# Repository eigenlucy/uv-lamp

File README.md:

# uv-lamp
Open source flashlight kit

Made with atopile/KiCad

Ordering UVA-UVC flashlights on Amazon is notoriously a crapshoot. This project is designed to enable easy use of quality diodes instead :)

You can order a kit or an assembled unit from my tindie store (soonTM), or find everything you need to print and enclosure and order PCB/PCBA services below

Gerbers, BOM, and CPL files for PCBA JLCPCB PCBA services are automatically generated on each push in the build artifacts under the Actions tab

# BMS+LED Driver board:
ato.yaml :: ccdriver

entry: elec/src/ccdriver.ato

Based on the [TI BQ24040](https://www.ti.com/lit/ds/symlink/bq24045.pdf) battery charger IC (LCSC ID: C2870255) and [TI TPS61169](https://www.ti.com/lit/ds/symlink/tps61169.pdf?ts=1737056749253) LED Driver (LSCS ID: C71045)

# LED PCB
ato.yaml :: default

entry: elec/src/uv-lamp.ato

This should be manufactured as a 1.6mm thick 1W aluminum PCB rated. You should use a hot plate to assemble this for sure.

V1 designed for 1-3 3535SMD LEDs on 1.6mm aluminum core PCBs, but see instructions below to easily adapt for use with any diode you like (power/space permitting).

# Mechanical
Heatsink:
[SV-LED-214E](https://www.digikey.com/en/products/detail/ohmite/SV-LED-214E/4301037), 3D model + datasheet in mech/SV-LED-214E

Mech BOM:

x3 2-56 UNC x 5mm screws

# Atopile usage
[Atopile Docs](https://docs.atopile.io/latest/)

Atopile makes it easy to adapt this design for use with other diodes, drivers, BMS circuits, etc.

To change the LED package:

1: Fork this repo

2: Install [atopile from pypi](https://pypi.org/project/atopile/0.2.5/) with uv (recommended), pipx, or virtual fish. There is also a VCS extension for those inclined. Follow the instructions in the ato docs on setting up the kicad plugin,usually just ```$ ato configure```

3: find diodes you want/diodes using the package you want on the JLCPCB parts library, LCSC, or with [this tool](https://yaqwsx.github.io/jlcparts/#/) and install them into your project directory with 
```$ ato install --jlcpcb <LCSC_ID>```
For example, to install [WS2812B Neopixels](https://jlcpcb.com/partdetail/Worldsemi-WS2812B2020/C965555) with LCSC ID C965555:
```$ ato install --jlcpcb C965555```

4: open uv-lamp.ato in a text editor. import the module/component you've installed, eg:
```from "WS2812B_minus_2020.ato" import WS2812B_minus_2020```
check the pin names in the component ato file, and configure and interfaces you need. For other UV diodes, just ensure the pins are labeled A (anode) and K (cathode) and replace the components assigned to led1-led3:
```led1 = new M3535N1UVS8U06_minus_365NM -> led1 = new <COMPONENT>```

5: build with ```$ ato build```. to use the graph viewer on a project with multiple builds, specify the target with ```$ ato view -t ccdriver```. default build is the LED PCB.

# Downloading PCB+PCBA files for JLCPCB
Gerbers, BOM and CPL files are automatically compiled at each build in the build artifacts of the Actions run. Each build (default for LED PCB, ccdriver for the BMS+LED Driver board) get its own set of files.

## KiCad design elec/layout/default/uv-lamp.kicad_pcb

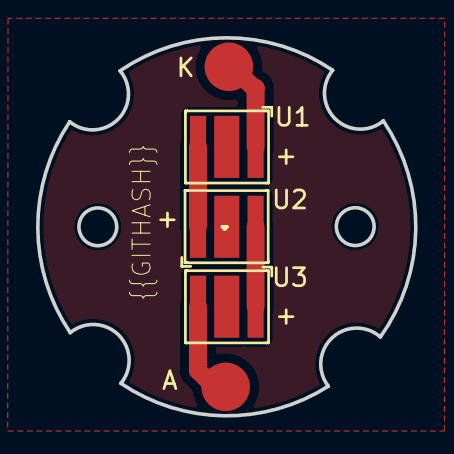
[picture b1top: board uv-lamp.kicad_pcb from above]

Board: 2 copper layers, 21.0 x 21.0 mm, 3 parts (0 on the bottom side), 2 nets.

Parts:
U1, U2, U3: LED-SMD_3P-L3.5-W3.5_M3535O1IRS13G06

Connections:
A-1: U1.1, U2.2
K: U2.1, U3.2

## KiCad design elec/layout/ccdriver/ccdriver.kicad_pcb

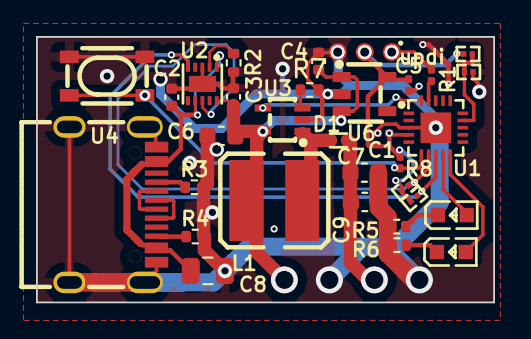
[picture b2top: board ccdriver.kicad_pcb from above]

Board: 2 copper layers, 25.4 x 14.8 mm, 31 parts (0 on the bottom side), 22 nets.

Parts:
C1: 10V 100nF X5R ±10% 0201 Multilayer Ceramic Capaci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; C0201
C2, C3, C4: 25V 1uF X5R ±10% 0402 Multilayer Ceramic Capacito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; C0402
C5: 10V 1uF X5R ±20% 0201 Multilayer Ceramic Capacito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; C0201
C6, C9: 16V 4.7uF X5R ±10% 0603 Multilayer Ceramic Capaci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; C0603
C7: 50V 1uF X5R ±10% 0603 Multilayer Ceramic Capacito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; C0603
C8: 25V 10uF X5R ±10% 0805 Multilayer Ceramic Capacit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; C0805
D1: ?; SOD-923_L0.8-W0.6-LS1.0-RD-1
L1: ?; IND-SMD_L4.5-W4.0
LED1, LED2: ?; LED0603-RD
R1: 50mW Thick Film Resistors ±5% 510Ω 0201 Chip Resi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; R0201
R2: 62.5mW Thick Film Resistors 50V ±100ppm/℃ ±1% 576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; R0402
R3, R4: 62.5mW Thick Film Resistors 50V ±100ppm/℃ ±1% 4.7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; R0402
R5: 62.5mW Thick Film Resistors 50V ±100ppm/℃ ±1% 220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; R0402
R6: 62.5mW Thick Film Resistors 50V ±1% ±200ppm/℃ 100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; R0402
R7: 62.5mW Thick Film Resistors 50V ±1% 300mΩ 0402 Ch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; R0402
R8, R9, R10, R11: 50mW Thick Film Resistors 25V ±1% ±200ppm/℃ 10kΩ 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; R0201
U1: ?; QFN-20_L3.0-W3.0-P0.40-TL-EP1.7
U2: ?; WSON-10_L2.0-W2.0-P0.40-BL-EP
U3: ?; SC-70-5_L2.1-W1.3-P0.65-LS2.1-BR
U4: ?; USB-C-SMD_KH-TYPE-C-16P
U5: ?; KEY-SMD_4P-L4.2-W3.2-P2.20-LS4.6
U6: ?; SOT-23-5_L3.0-W1.7-P0.95-LS2.8-TL
U7: ?; R0201

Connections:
bms.ic-vcc: C2.1, C8.1, U2.1, U2.7, U4.A4, U4.A9, U4.B4, U4.B9
cc1: R3.1, U4.A5
cc2: R4.1, U4.B5
charge_led.resistor-cathode: LED1.1, R5.1
chg: R10.1, U1.7, U2.8
ctrl: U1.20, U3.4
dm: U4.A7, U4.B7
dp: U4.A6, U4.B6
fb: R7.1, U3.3
full_led.resistor-cathode: LED2.1, R6.1
gnd: C1.2, C2.2, C3.2, C4.2, C5.2, C6.2, C7.2, C8.2, C9.2, R2.2, R3.2, R4.2, R5.2, R6.2, R7.2, U1.3, U1.21, U2.3, U2.11, U3.2, U4.1, U4.2, U4.3, U4.4, U4.A1, U4.A12, U4.B1, U4.B12, U5.3, U5.4, U6.2, U7.2
in: R8.1, U1.6, U5.1, U5.2
iset: R2.1, U2.2
pa0_reset_updi: R1.2, U1.19
pg: R11.1, U1.8, U2.5
sw: D1.2, L1.2, U3.1
temp: R9.2, U1.14, U7.1
uc.ic-vcc: C1.1, C5.1, R8.2, R9.1, R10.2, R11.2, U1.4, U6.5
uc.ic-vcc-1: LED1.2, U1.9
uc.ic-vcc-2: LED2.2, U1.10
vcc: C7.1, C9.1, D1.1
vcc-1: C3.1, C4.1, C6.1, L1.1, U2.10, U3.5, U6.1, U6.3

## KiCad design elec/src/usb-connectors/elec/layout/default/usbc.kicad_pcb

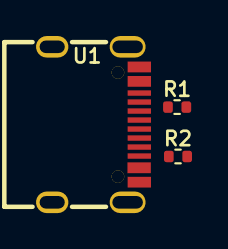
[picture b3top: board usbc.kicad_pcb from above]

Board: 2 copper layers, 3 parts (0 on the bottom side), 6 nets, no tracks yet.

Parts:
R1, R2: Chip Resistor - Surface Mount 4.7KOhms ±5% 1/16W 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; R0402
U1: USB-C-SMD_KH-TYPE-C-16P

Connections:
cc1: R1.1, U1.A5
cc2: R2.1, U1.B5
dm: U1.A7, U1.B7
dp: U1.A6, U1.B6
gnd: R1.2, R2.2, U1.1, U1.2, U1.3, U1.4, U1.A1, U1.A12, U1.B1, U1.B12
vcc: U1.A4, U1.A9, U1.B4, U1.B9

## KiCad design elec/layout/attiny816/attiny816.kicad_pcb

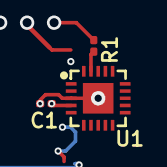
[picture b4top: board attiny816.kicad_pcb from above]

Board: 2 copper layers, 3 parts (0 on the bottom side), 3 nets.

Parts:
C1: 25V 100nF X5R ±10% 0201 Multilayer Ceramic Capaci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; C0201
R1: 50mW Thick Film Resistors ±5% 510Ω 0201 Chip Resi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; R0201
U1: ?; QFN-20_L3.0-W3.0-P0.40-TL-EP1.7

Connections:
gnd: C1.2, U1.3, U1.21
pa0_reset_updi: R1.2, U1.19
vcc: C1.1, U1.4

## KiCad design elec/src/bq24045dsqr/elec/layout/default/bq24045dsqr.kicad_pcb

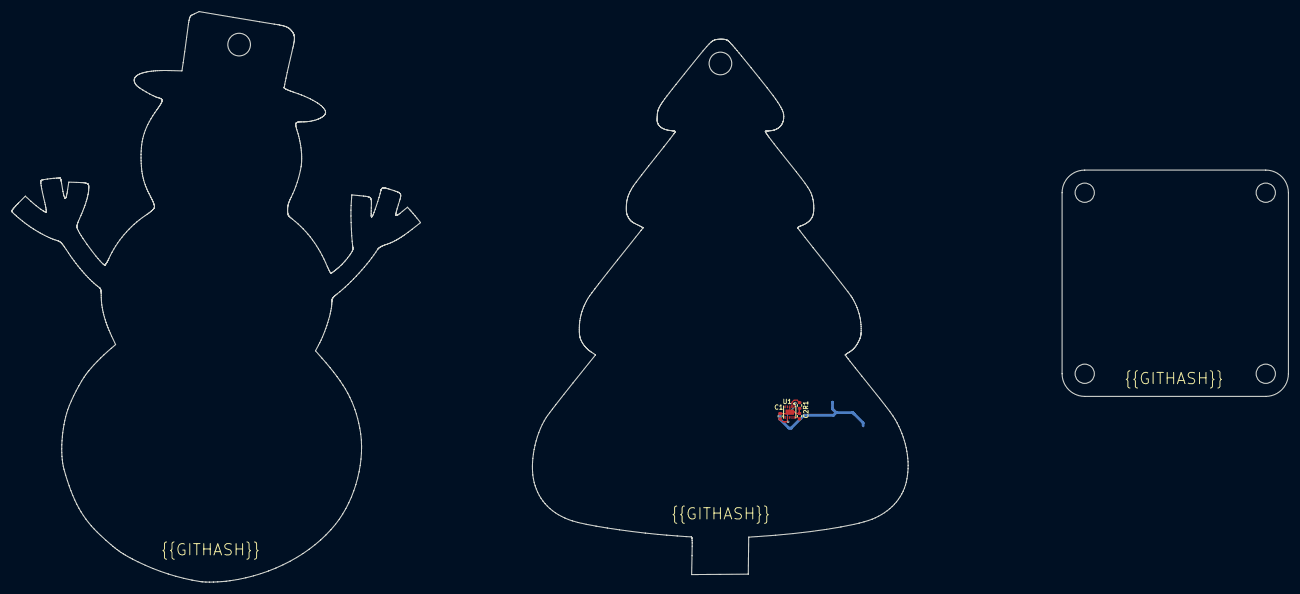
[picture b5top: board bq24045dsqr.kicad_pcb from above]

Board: 2 copper layers, 66.4 x 94.6 mm, 4 parts (0 on the bottom side), 4 nets.

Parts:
C1, C2: 25V 1uF X5R ±10% 0402 Multilayer Ceramic Capacito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; C0402
R1: 100mW Thick Film Resistors ±100ppm/℃ ±1% 604Ω 040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; R0402
U1: WSON-10_L2.0-W2.0-P0.40-BL-EP

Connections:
ic-gnd: C1.2, C2.2, R1.2, U1.3, U1.11
ic-vcc: C1.1, U1.1, U1.7
ic-vcc-1: C2.1, U1.10
iset: R1.1, U1.2

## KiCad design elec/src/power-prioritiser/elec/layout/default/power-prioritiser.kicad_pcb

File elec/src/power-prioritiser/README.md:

# Power Prioritiser ⚡️

A simple circuit to prioritise a power source over another.

This is useful for situations like a USB-charged battery operated device, where you also want it to work when connected over just USB power.

Often, cheap (and annoyingly expensive) devices neglect this circuit and shutdown when connected over USB. I find this infuriating!

This is better than merely pulling power through the charger circuit because often the inrush currents of a circuit will overwhelm the charger IC and cause it to shut down. This can even lead in the nastiest cases to a boot-loop where the device never charges from a 0% battery.

It's better than a diode because it can handle high-voltage low-priority sources than high and it doesn't have a voltage drop over the low-priority source (typically a battery).

## Limitations

Currently, the components for this circuit are bespokely selected, and aren't parametised for majorly different voltages and currents. It's designed for a USB charged, 1S LiPo powered device.

## Usage

Simple! Hook up `high_priority` and `low_priority` to your power sources, and `out` to your device.

## How it works

When the high-priority power source is connected, the P-FET's gate is pulled high, turning it off. The P-FET thereby stops the low-priority power source from powering the device, even if it's voltage is higher than the high-priority source.

### Both sources connected

### High-priority source only

### Low-priority source only

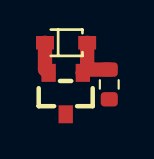
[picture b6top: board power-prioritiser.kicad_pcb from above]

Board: 2 copper layers, 3 parts (0 on the bottom side), 2 nets.

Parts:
DS1: ?; SOD-323_L1.8-W1.3-LS2.5-RD
Q1: ?; SOT-23_L2.9-W1.3-P1.90-LS2.4-BR
R1: 100mW Thick Film Resistors 75V ±100ppm/℃ ±1% 10kΩ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; R0603

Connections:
vcc: DS1.2, Q1.1, R1.1
vcc-2: DS1.1, Q1.2

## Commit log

2025-01-16 Configure project
2025-01-16 initial commit, ordering diode board to test heatsink fit and thermals
2025-01-16 readme
2025-01-16 silkscreened githash
2025-01-16 adjusted holes
2025-01-16 removed uv-lamp build PCB bottom layer
2025-01-16 freecad attempts
2025-01-17 fixed..tab
2025-01-17 LEDs in series, fixed ccdriver errors
2025-01-17 added bms
2025-01-17 ato documentation
2025-01-18 edited cc driver
2025-01-21 ccdriver
2025-01-21 ccdriver updates
2025-01-22 added 3v reg + layout edits
2025-01-23 adding notches to driver
2025-01-24 new uv PCB
2025-01-24 ccdriver edits
2025-01-26 cc driver planes
2025-01-26 added ccdriver~bms io connections
2025-01-27 fixed projects
2025-01-27 fixed ground plane
2025-01-27 changed r7 to 0402
2025-01-27 new step models
2025-01-27 fixed maybe
2025-01-27 updated usb package
2025-01-27 fixed usbc and vias
2025-01-29 fixing 3d models
2025-02-18 error checking
